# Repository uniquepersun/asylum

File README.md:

# asylum
placeholder repo for Hack Club's asylum YSWS (zach plz make the real one)

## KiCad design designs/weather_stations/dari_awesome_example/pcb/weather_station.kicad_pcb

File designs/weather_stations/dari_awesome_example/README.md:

# dari // alexren's super cool weather station submission

Here's my submission for my weather station! Tentatively calling it raincloud

## Features:
- Displays:
    - Moon phases
    - Temperature 
    - Icons
- 8 WS2812Bs for dynamic LED effects
- A switch to swap between Freedom units and regular human units
- Breakout pins to add an indoor temp sensor + UART breakouts

## PCB
Here's a picture of my schematic! I wired a Wemos ESP32-C3* module to a TFT display, 8 WS2812B LEDs, a switch for Farenheit vs Celsius, and broken out headers for a DHT22 Sensor!

Schematic            |  PCB
:-------------------------:|:-------------------------:
  |  

*For my actual build, I'm using a WeMos ESP32-S3 module instead since it's cheaper and I don't need the bluetooth functionality! As a bonus theres 2x the amount of GPIO to work with if I ned to in the future.

[ x ] I ran DRC in KiCad and have made sure there are 0 errors!

## CAD Model:
Everything fits together using 4 M3 Heatset inserts and 4 M3x16mm screws. Here's how it looks:

(insert image here)

It was made in fusion360 pretty nifty stuff.

## Firmware overview
The firmware for this is written in Arduino. It grabs the weather info using an api request to mateoweather. Then, it uses the Adafruit_GFX library to push the data to the screen

[ x ] I remembered to exclude any personal information, including API Keys, WiFi passwords, etc

## BOM
All prices must be in USD.

Provided by dari // alex:
- 1x WeMos S2 Mini (as a cheaper replacement for the S2) WITHOUT FEMALE HEADERS
- 1x ST7735 1.8" LCD display WITHOUT FEMALE HEADERS. Male headers soldered!
- 1x 3D printed case

Purchasing from HQ:
- 8x WS2812Bs at $0.20/per. I will be losing $1.6 from my grant as a result.

I will be sourcing the following parts with my grant:
- 1x PCB from JLCPCB
    - $2 for 5x + $1.50 shipping
- 1x SPDT slide switch [(LCSC)](https://www.lcsc.com/product-detail/Slide-Switches_G-Switch-SS-12E17-G020_C2848909.html) $0.44 (min order 5)
- 3x 1x8 female headers for my ST7735 display [(LCSC)](https://www.lcsc.com/product-detail/Female-Headers_BOOMELE-Boom-Precision-Elec-2-54-1-8P_C27438.html) $0.70 (min order 10)

Shipping from LCSC: $7.72 + $3 small order fee

Total before tax: $16.96

I'll also be source the following parts myself since I already have them and would like to help Hack Club:
- 4x M3x16mm BHCS screws
- Some solid-core wire to wire the slide switch together
- 4x M3x5mmx4mm heatset inserts

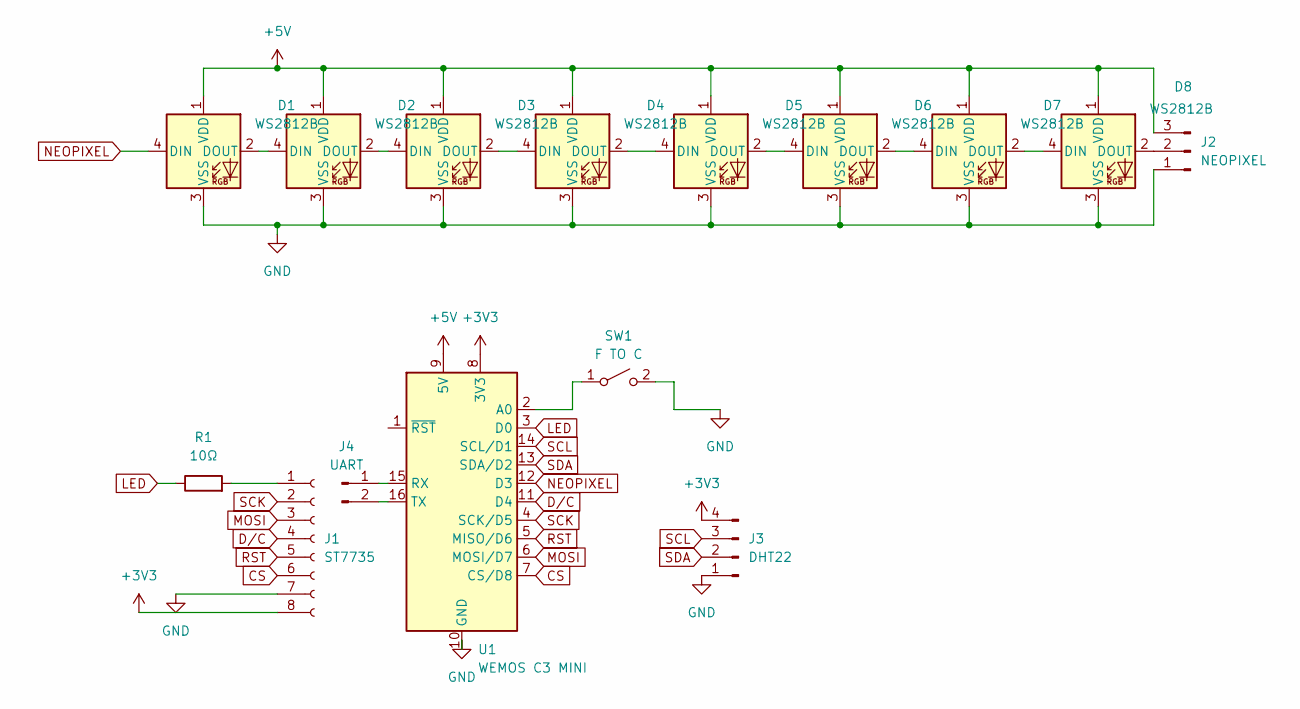
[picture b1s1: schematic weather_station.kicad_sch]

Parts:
D1, D2, D3, D4, D5, D6, D7, D8: WS2812B; LED_WS2812B_PLCC4_5.0x5.0mm_P3.2mm
J1: ST7735; TFT_ST7735_SD
J2: NEOPIXEL; PinHeader_1x03_P2.54mm_Vertical
J3: DHT22; PinHeader_1x04_P2.54mm_Vertical
J4: UART; PinHeader_1x02_P2.54mm_Vertical
R1: 10Ω; R_Axial_DIN0207_L6.3mm_D2.5mm_P7.62mm_Horizontal
SW1: F TO C; PinHeader_1x02_P2.54mm_Vertical
U1: WEMOS C3 MINI; WEMOS_C3_mini

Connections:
+3V3: J1.8, J3.4, U1.8 (3V3)
+5V: D1.1 (VDD), D2.1 (VDD), D3.1 (VDD), D4.1 (VDD), D5.1 (VDD), D6.1 (VDD), D7.1 (VDD), D8.1 (VDD), J2.3, U1.9 (5V)
CS: J1.6, U1.7 (CS/D8)
D/C: J1.4, U1.11 (D4)
GND: D1.3 (VSS), D2.3 (VSS), D3.3 (VSS), D4.3 (VSS), D5.3 (VSS), D6.3 (VSS), D7.3 (VSS), D8.3 (VSS), J1.7, J2.1, J3.1, SW1.2 (B), U1.10 (GND)
LED: R1.1, U1.3 (D0)
MOSI: J1.3, U1.6 (MOSI/D7)
NEOPIXEL: D1.4 (DIN), U1.12 (D3)
unnamed: D1.2 (DOUT), D2.4 (DIN)
unnamed: D2.2 (DOUT), D3.4 (DIN)
unnamed: D3.2 (DOUT), D4.4 (DIN)
unnamed: D4.2 (DOUT), D5.4 (DIN)
unnamed: D5.2 (DOUT), D6.4 (DIN)
unnamed: D6.2 (DOUT), D7.4 (DIN)
unnamed: D7.2 (DOUT), D8.4 (DIN)
unnamed: D8.2 (DOUT), J2.2
unnamed: J1.1, R1.2
unnamed: J4.1, U1.15 (RX)
unnamed: J4.2, U1.16 (TX)
unnamed: SW1.1 (A), U1.2 (A0)
RST: J1.5, U1.5 (MISO/D6)
SCK: J1.2, U1.4 (SCK/D5)
SCL: J3.3, U1.14 (SCL/D1)
SDA: J3.2, U1.13 (SDA/D2)

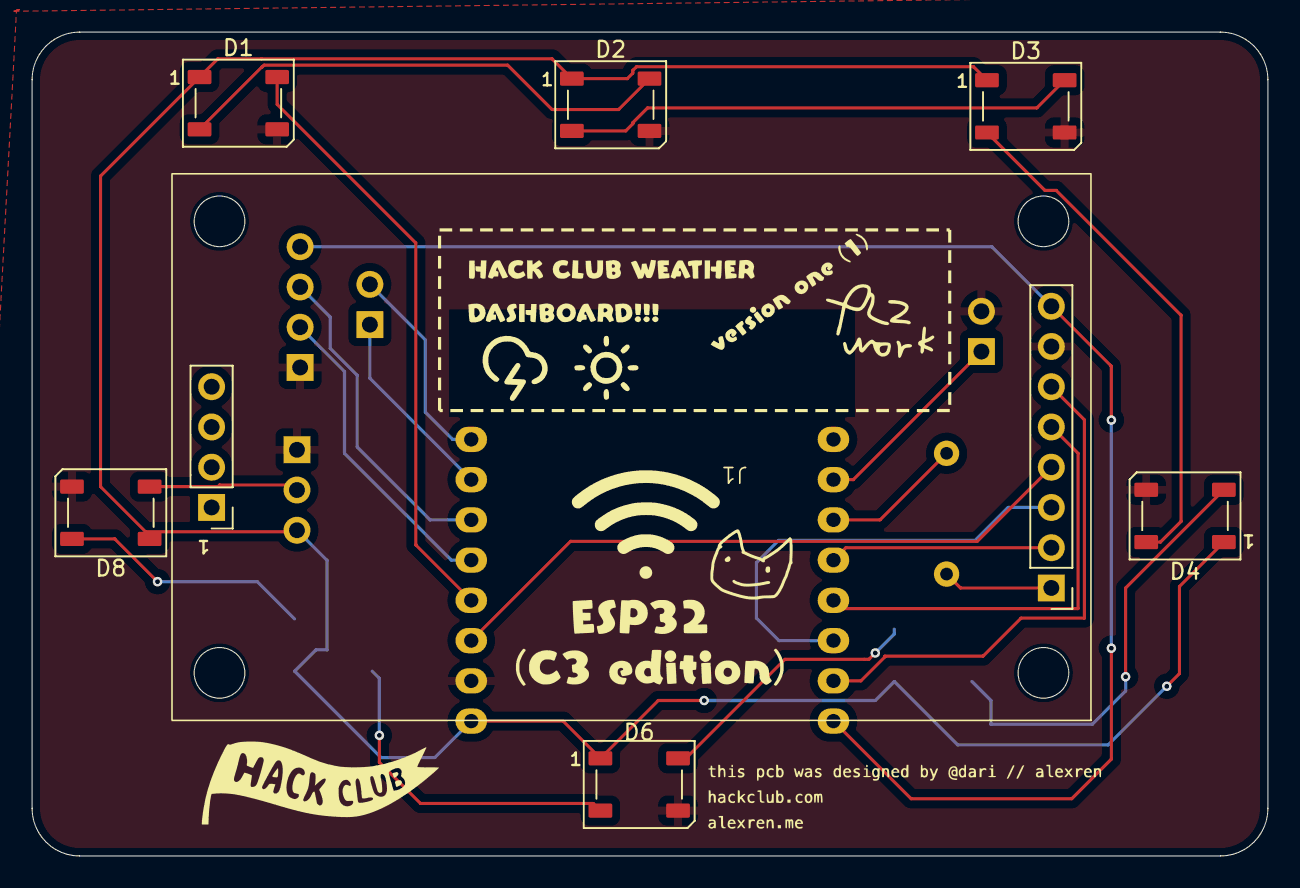
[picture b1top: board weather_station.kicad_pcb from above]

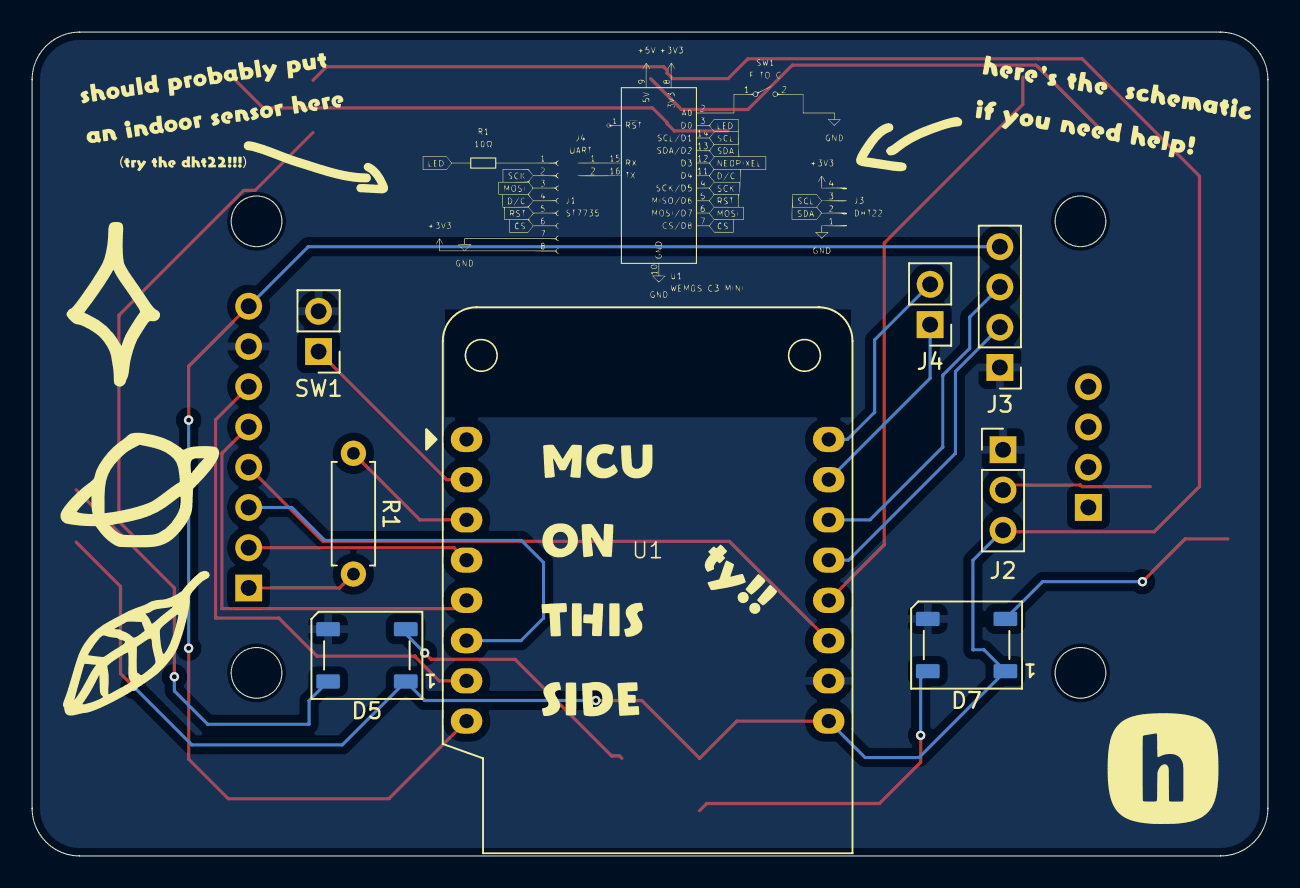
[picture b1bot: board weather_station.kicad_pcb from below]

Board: 2 copper layers, 78.0 x 52.0 mm, 15 parts (8 on the bottom side), 24 nets.

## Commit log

2024-12-16 added pcb for example
2024-12-23 added nfc keychain thing
2025-01-13 added kaychain.step
2025-01-20 updated weather station example
2025-01-20 updated added assets whoops
2025-01-25 updated files?? idk
2025-01-25 syncing w/ desktop
2025-01-25 updated examples
2025-01-27 added automation
2025-01-27 renamed comment message to fix workflow
2025-01-27 updated workflows
2025-01-27 i give up trying to delete the comments. rest in piss
2025-01-27 [ImgBot] Optimize images
    *Total -- 1,280.44kb -> 756.19kb (40.94%)
    /designs/weather_stations/dari_awesome_example/pcb/libs/indoor sensor.png -- 91.86kb -> 39.78kb (56.7%)
    /designs/weather_stations/dari_awesome_example/pcb/libs/schematic.png -- 12.01kb -> 5.77kb (51.96%)
    /designs/weather_stations/dari_awesome_example/pcb/libs/plzwokr.png -- 22.51kb -> 10.97kb (51.26%)
    /designs/weather_stations/dari_awesome_example/pcb/libs/plzwork2.png -- 27.93kb -> 13.72kb (50.87%)
    /designs/weather_stations/dari_awesome_example/assets/schematic.png -- 130.84kb -> 65.83kb (49.68%)
